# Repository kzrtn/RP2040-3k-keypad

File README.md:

# RP2040 3k keypad
 A 3 key macropad using RP2040 for osu!

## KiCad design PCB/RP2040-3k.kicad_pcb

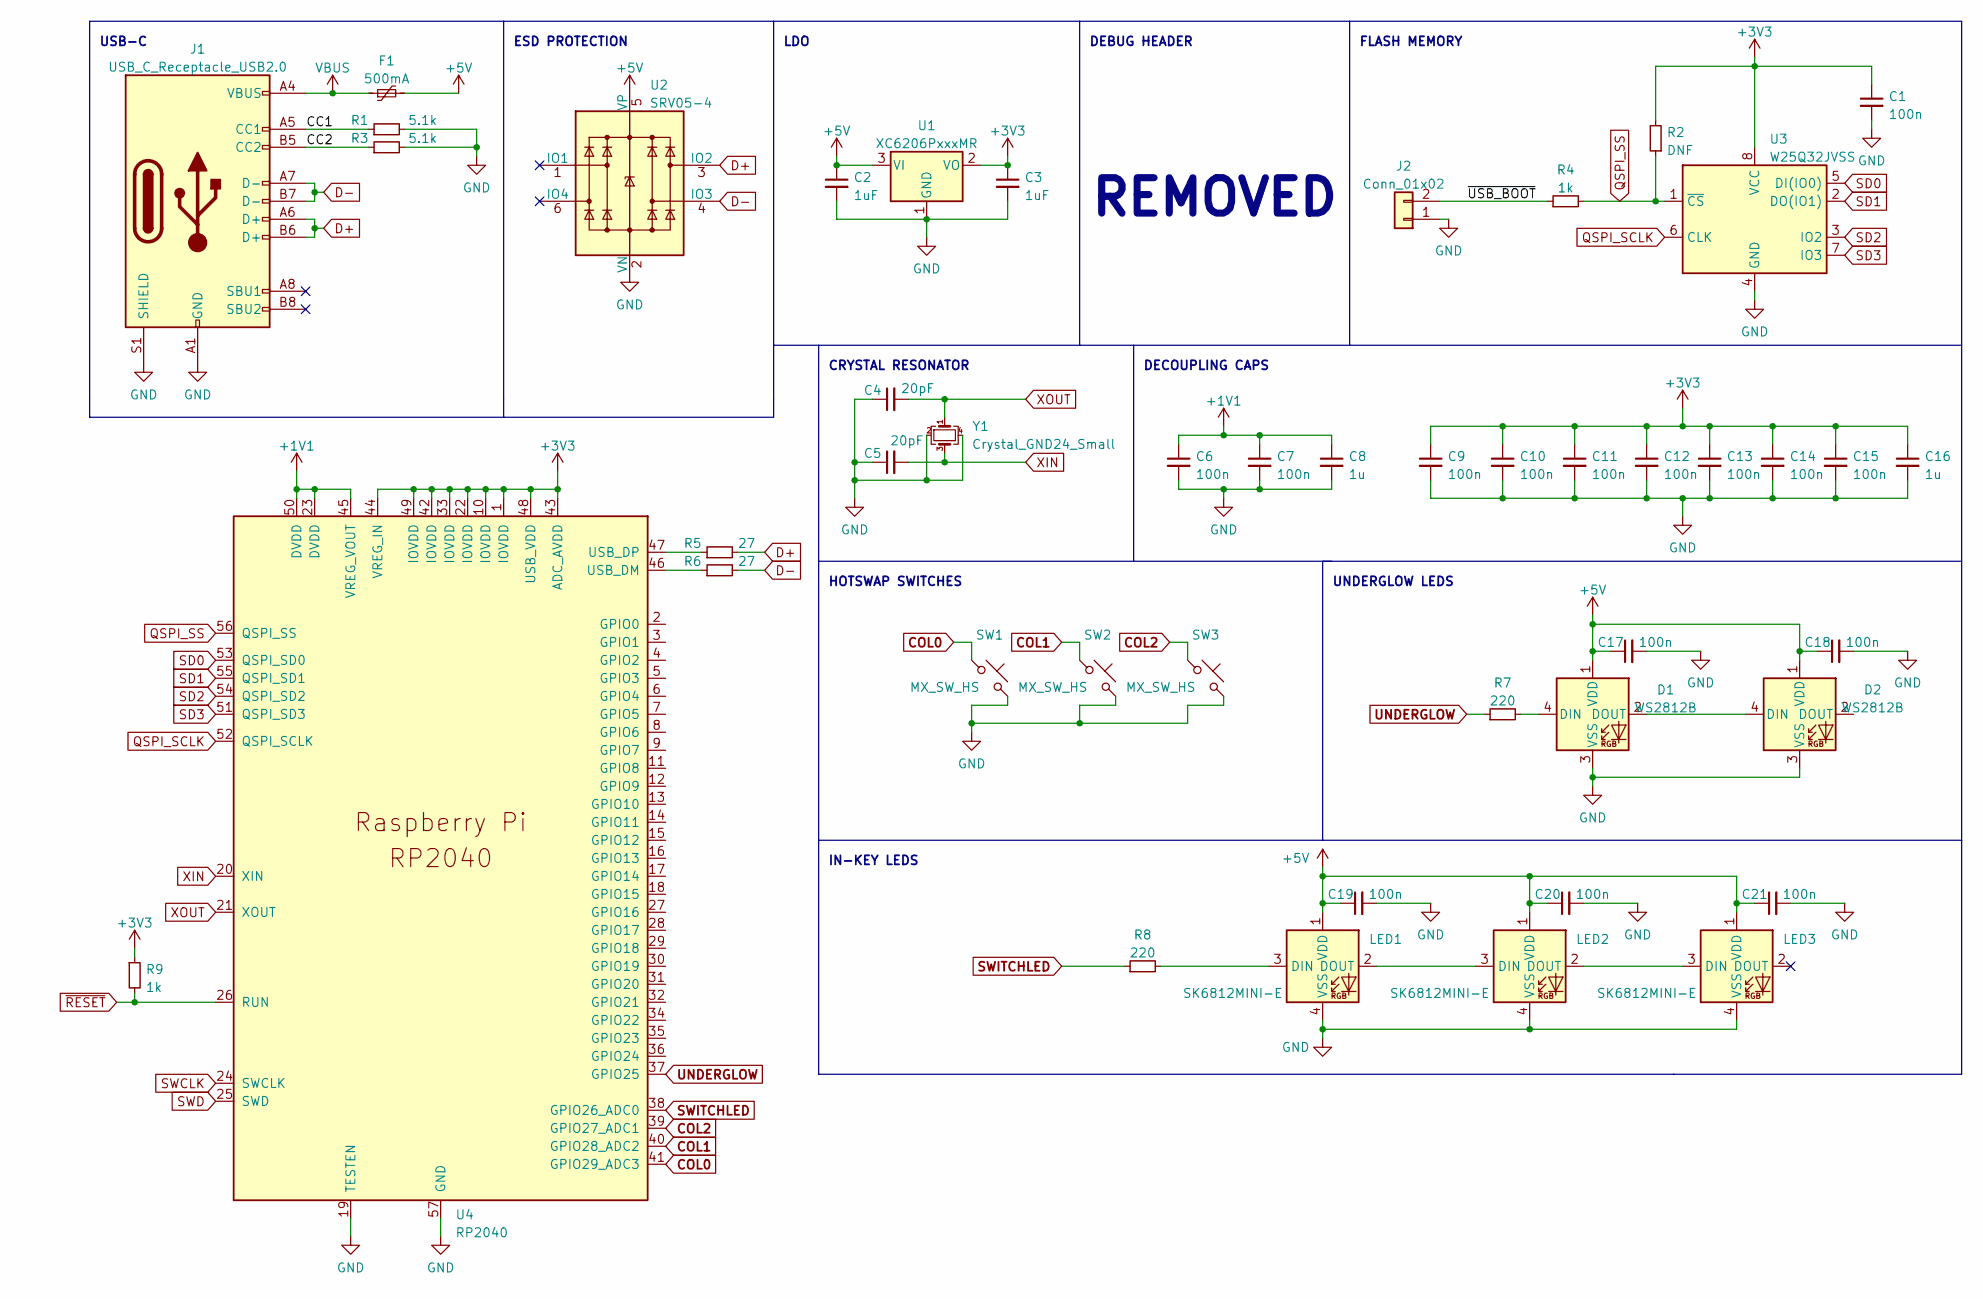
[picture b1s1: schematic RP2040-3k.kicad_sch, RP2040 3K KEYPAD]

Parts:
C1, C6, C7, C9, C10, C11, C12, C13, C14, C15, C17, C18, C19, C20, C21: 100n; C_0402_1005Metric
C2, C3: 1uF; C_0402_1005Metric
C4, C5: 20pF; C_0402_1005Metric
C8, C16: 1u; C_0402_1005Metric
D1, D2: WS2812B; LED_WS2812B_PLCC4_5.0x5.0mm_P3.2mm
F1: 500mA; Fuse_0402_1005Metric
J1: USB_C_Receptacle_USB2.0; USB_C_Receptacle_HRO_TYPE-C-31-M-12
J2: Conn_01x02; PinHeader_1x02_P2.54mm_Vertical
LED1, LED2, LED3: SK6812MINI-E; LED_6028R
R1, R3: 5.1k; R_0402_1005Metric
R2: DNF; R_0402_1005Metric
R4, R9: 1k; R_0402_1005Metric
R5, R6: 27; R_0402_1005Metric
R7, R8: 220; R_0402_1005Metric
SW1, SW2, SW3: MX_SW_HS; SW_MX_HS_1u
U1: XC6206PxxxMR; SOT-23
U2: SRV05-4; SOT-23-6-routable
U3: W25Q32JVSS; SOIC-8_5.23x5.23mm_P1.27mm
U4: RP2040; RP2040-QFN-56
Y1: Crystal_GND24_Small; Crystal_SMD_3225-4Pin_3.2x2.5mm

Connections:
+1V1: C6.1, C7.1, C8.1, U4.23 (DVDD), U4.45 (VREG_VOUT), U4.50 (DVDD)
+3V3: C1.1, C3.1, C9.1, C10.1, C11.1, C12.1, C13.1, C14.1, C15.1, C16.1, R2.2, R9.1, U1.2 (VO), U3.8 (VCC), U4.1 (IOVDD), U4.10 (IOVDD), U4.22 (IOVDD), U4.33 (IOVDD), U4.42 (IOVDD), U4.43 (ADC_AVDD), U4.44 (VREG_IN), U4.48 (USB_VDD), U4.49 (IOVDD)
+5V: C2.1, C17.1, C18.1, C19.1, C20.1, C21.1, D1.1 (VDD), D2.1 (VDD), F1.2, LED1.1 (VDD), LED2.1 (VDD), LED3.1 (VDD), U1.3 (VI), U2.5 (VP)
/CC1: J1.A5 (CC1), R1.1
/CC2: J1.B5 (CC2), R3.1
/~USB_BOOT: J2.2, R4.1
COL0: SW1.1, U4.41 (GPIO29_ADC3)
COL1: SW2.1, U4.40 (GPIO28_ADC2)
COL2: SW3.1, U4.39 (GPIO27_ADC1)
D+: J1.A6 (D+), J1.B6 (D+), R5.2, U2.3 (IO2)
D-: J1.A7 (D-), J1.B7 (D-), R6.2, U2.4 (IO3)
GND: C1.2, C2.2, C3.2, C4.1, C5.1, C6.2, C7.2, C8.2, C9.2, C10.2, C11.2, C12.2, C13.2, C14.2, C15.2, C16.2, C17.2, C18.2, C19.2, C20.2, C21.2, D1.3 (VSS), D2.3 (VSS), J1.A1 (GND), J1.A12 (GND), J1.B1 (GND), J1.B12 (GND), J1.S1 (SHIELD), J2.1, LED1.4 (VSS), LED2.4 (VSS), LED3.4 (VSS), R1.2, R3.2, SW1.2, SW2.2, SW3.2, U1.1 (GND), U2.2 (VN), U3.4 (GND), U4.19 (TESTEN), U4.57 (GND), Y1.2, Y1.4
unnamed: D1.2 (DOUT), D2.4 (DIN)
unnamed: D1.4 (DIN), R7.2
unnamed: LED1.2 (DOUT), LED2.3 (DIN)
unnamed: LED1.3 (DIN), R8.2
unnamed: LED2.2 (DOUT), LED3.3 (DIN)
unnamed: R5.1, U4.47 (USB_DP)
unnamed: R6.1, U4.46 (USB_DM)
QSPI_SCLK: U3.6 (CLK), U4.52 (QSPI_SCLK)
QSPI_SS: R2.1, R4.2, U3.1 (~CS), U4.56 (QSPI_SS)
SD0: U3.5 (DI(IO0)), U4.53 (QSPI_SD0)
SD1: U3.2 (DO(IO1)), U4.55 (QSPI_SD1)
SD2: U3.3 (IO2), U4.54 (QSPI_SD2)
SD3: U3.7 (IO3), U4.51 (QSPI_SD3)
SWCLK: U4.24 (SWCLK)
SWD: U4.25 (SWD)
SWITCHLED: R8.1, U4.38 (GPIO26_ADC0)
UNDERGLOW: R7.1, U4.37 (GPIO25)
VBUS: F1.1, J1.A4 (VBUS), J1.A9 (VBUS), J1.B4 (VBUS), J1.B9 (VBUS)
XIN: C5.2, U4.20 (XIN), Y1.3
XOUT: C4.2, U4.21 (XOUT), Y1.1
~RESET: R9.2, U4.26 (RUN)

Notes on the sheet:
IN-KEY LEDS
REMOVED
DEBUG HEADER
USB-C
UNDERGLOW LEDS
HOTSWAP SWITCHES
FLASH MEMORY
ESD PROTECTION
CRYSTAL RESONATOR
DECOUPLING CAPS
LDO

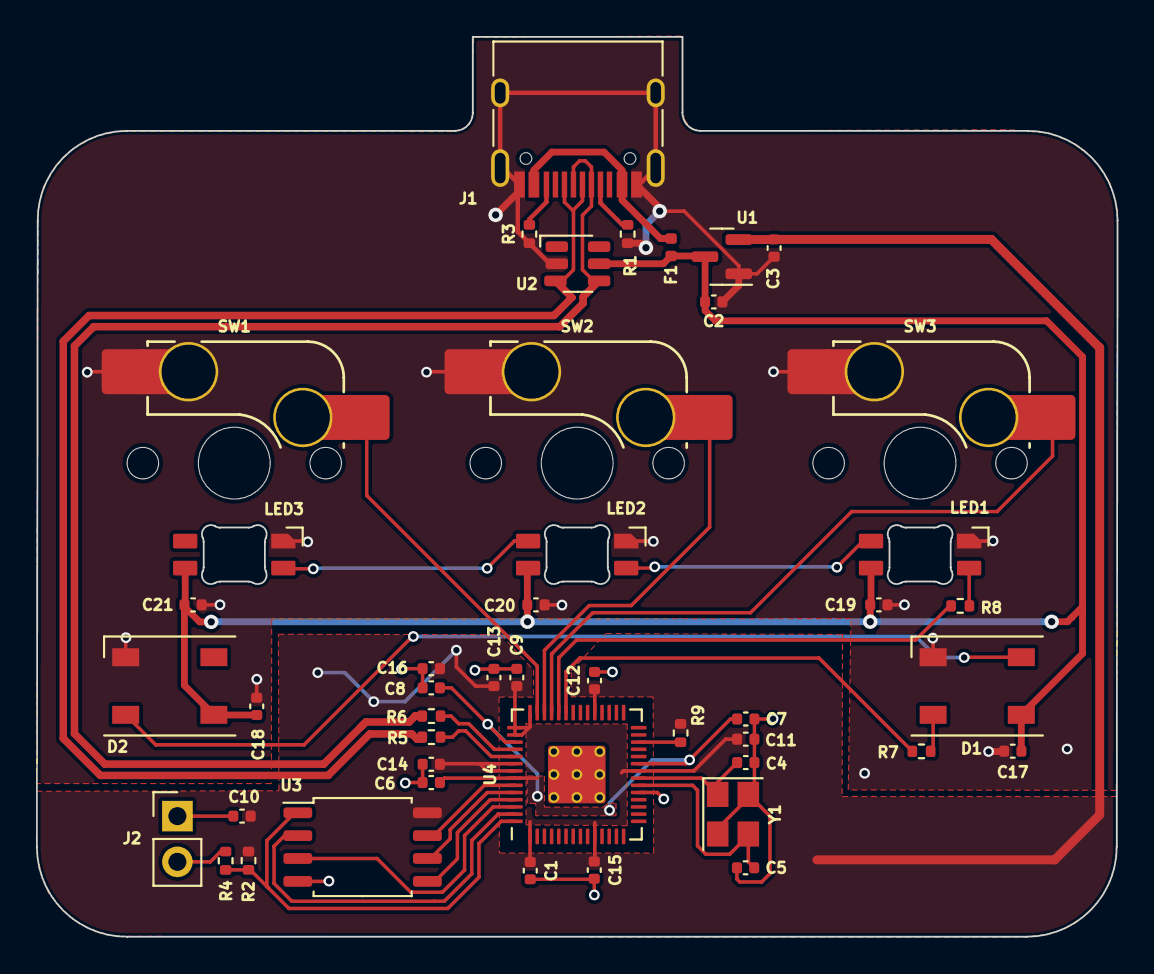
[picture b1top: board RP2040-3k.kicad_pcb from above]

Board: 2 copper layers, 60.0 x 50.0 mm, 46 parts (0 on the bottom side), 31 nets.

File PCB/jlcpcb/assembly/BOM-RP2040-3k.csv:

Comment,Designator,Footprint,LCSC
SK6812MINI-E,LED3,LED_6028R,
1u,C16,C_0402_1005Metric,
5.1k,R1,R_0402_1005Metric,
XC6206PxxxMR,U1,SOT-23,
DNF,R2,R_0402_1005Metric,
RP2040,U4,RP2040-QFN-56,
100n,C6,C_0402_1005Metric,
100n,C11,C_0402_1005Metric,
Crystal_GND24_Small,Y1,Crystal_SMD_3225-4Pin_3.2x2.5mm,
1u,C8,C_0402_1005Metric,
100n,C20,C_0402_1005Metric,
20pF,C4,C_0402_1005Metric,
100n,C7,C_0402_1005Metric,
100n,C15,C_0402_1005Metric,
20pF,C5,C_0402_1005Metric,
100n,C1,C_0402_1005Metric,
WS2812B,D1,LED_WS2812B_PLCC4_5.0x5.0mm_P3.2mm,
27,R5,R_0402_1005Metric,
100n,C21,C_0402_1005Metric,
27,R6,R_0402_1005Metric,
100n,C17,C_0402_1005Metric,
100n,C10,C_0402_1005Metric,
500mA,F1,Fuse_0402_1005Metric,
Conn_01x02,J2,PinHeader_1x02_P2.54mm_Vertical,
100n,C12,C_0402_1005Metric,
1k,R4,R_0402_1005Metric,
1k,R9,R_0402_1005Metric,
1uF,C2,C_0402_1005Metric,
WS2812B,D2,LED_WS2812B_PLCC4_5.0x5.0mm_P3.2mm,
5.1k,R3,R_0402_1005Metric,
100n,C18,C_0402_1005Metric,
SK6812MINI-E,LED2,LED_6028R,
SRV05-4,U2,SOT-23-6-routable,
1uF,C3,C_0402_1005Metric,
MX_SW_HS,SW1,SW_MX_HS_1u,
MX_SW_HS,SW2,SW_MX_HS_1u,
W25Q32JVSS,U3,SOIC-8_5.23x5.23mm_P1.27mm,
100n,C9,C_0402_1005Metric,
SK6812MINI-E,LED1,LED_6028R,
100n,C19,C_0402_1005Metric,
100n,C13,C_0402_1005Metric,
MX_SW_HS,SW3,SW_MX_HS_1u,
220,R7,R_0402_1005Metric,
100n,C14,C_0402_1005Metric,
USB_C_Receptacle_USB2.0,J1,USB_C_Receptacle_HRO_TYPE-C-31-M-12,
220,R8,R_0402_1005Metric,

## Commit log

2022-05-26 Created project and added libraries
2022-05-26 Schematic and PCB progress
    Schematic is done. Most likely requires the debug header to be redone. PCB has dimensions and components laid out. USB-C port has only been routed
2022-05-26 Finished routing PCB
    W25Q16JVUXIQTR library removed. Not using that part. Dimension changes made and other schematic things.
2022-05-27 Redid traces to tolerance
    Clearance is now 0.2mm across the board. I also generated gerber files and etc
2022-06-17 Fixed values and redid traces
    Changed the data traces to be thicker. Redid crystal capacitor values (I originally calculated them wrongly). Changed 0.1uF values to 100nF for consistency. Regenerated BOM with updated changes
2022-06-17 Updated Gerber
2022-07-04 Removed step up and fixed capacitor values
2022-07-19 Fixed case files and added .dxf version
    The layer that held the PCB is made smaller to fit the PCB better. USB cut out is made consistent and the hole for the reset pins are now actually properly sized and put where it is.
